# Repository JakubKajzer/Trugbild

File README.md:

# Trugbild
A FPGA working in serial with HDMI, for some real live video modifications. I'm making it to prove myself, that I can route highspeed PCB and to learn to code FPGA better.

## Features

- Xilinx Spartan 3 XC3S50A
- 2MB Flash memory
- 32MB DRAM memory
- Possibility to power device only from HDMI or from external input

## PCB screenshots
|||
|---|---|
## Why "Trugbild"
It is because Trugbild is a german word meaning _illusion_. So I think that is a good name for device which can modify what you see :)

## Develop steps
- [x] Make PCB

- [x] Order PCB fabrication
- [ ] Order elements
- [ ] Solder everything
- [ ] First run
- [ ] Try to run device only with power from HDMI (max. 50mA@5V)
- [ ] Make and test if device can transmit HDMI at Full HD
- [ ] Make some video modification while transmitting
- [ ] Try to add some kind of neuron network to face recognition
- [ ] Try to cover detected faces with some picture or someone face :)
## Comments
### Make PCB
This point took me many hours of designing because this is my first design with FPGA, so I had pretty much to learn. I'm still not sure if everything was routed least good, but I will find it out soon.
### Order PCB fabrication
For this, I used JLCPCB. They have 3.5mils clearance and track width, 0.2mm holes minimum, and four layers just for 8$. That's incredible!
But after uploading gerber files, it comes that they don't have 3.5mils clearance, but 0.09mm (3.543mils), so I must re-route some nets on PCB :( The 5 PCBs cost me total of $15.89 with delivery included.

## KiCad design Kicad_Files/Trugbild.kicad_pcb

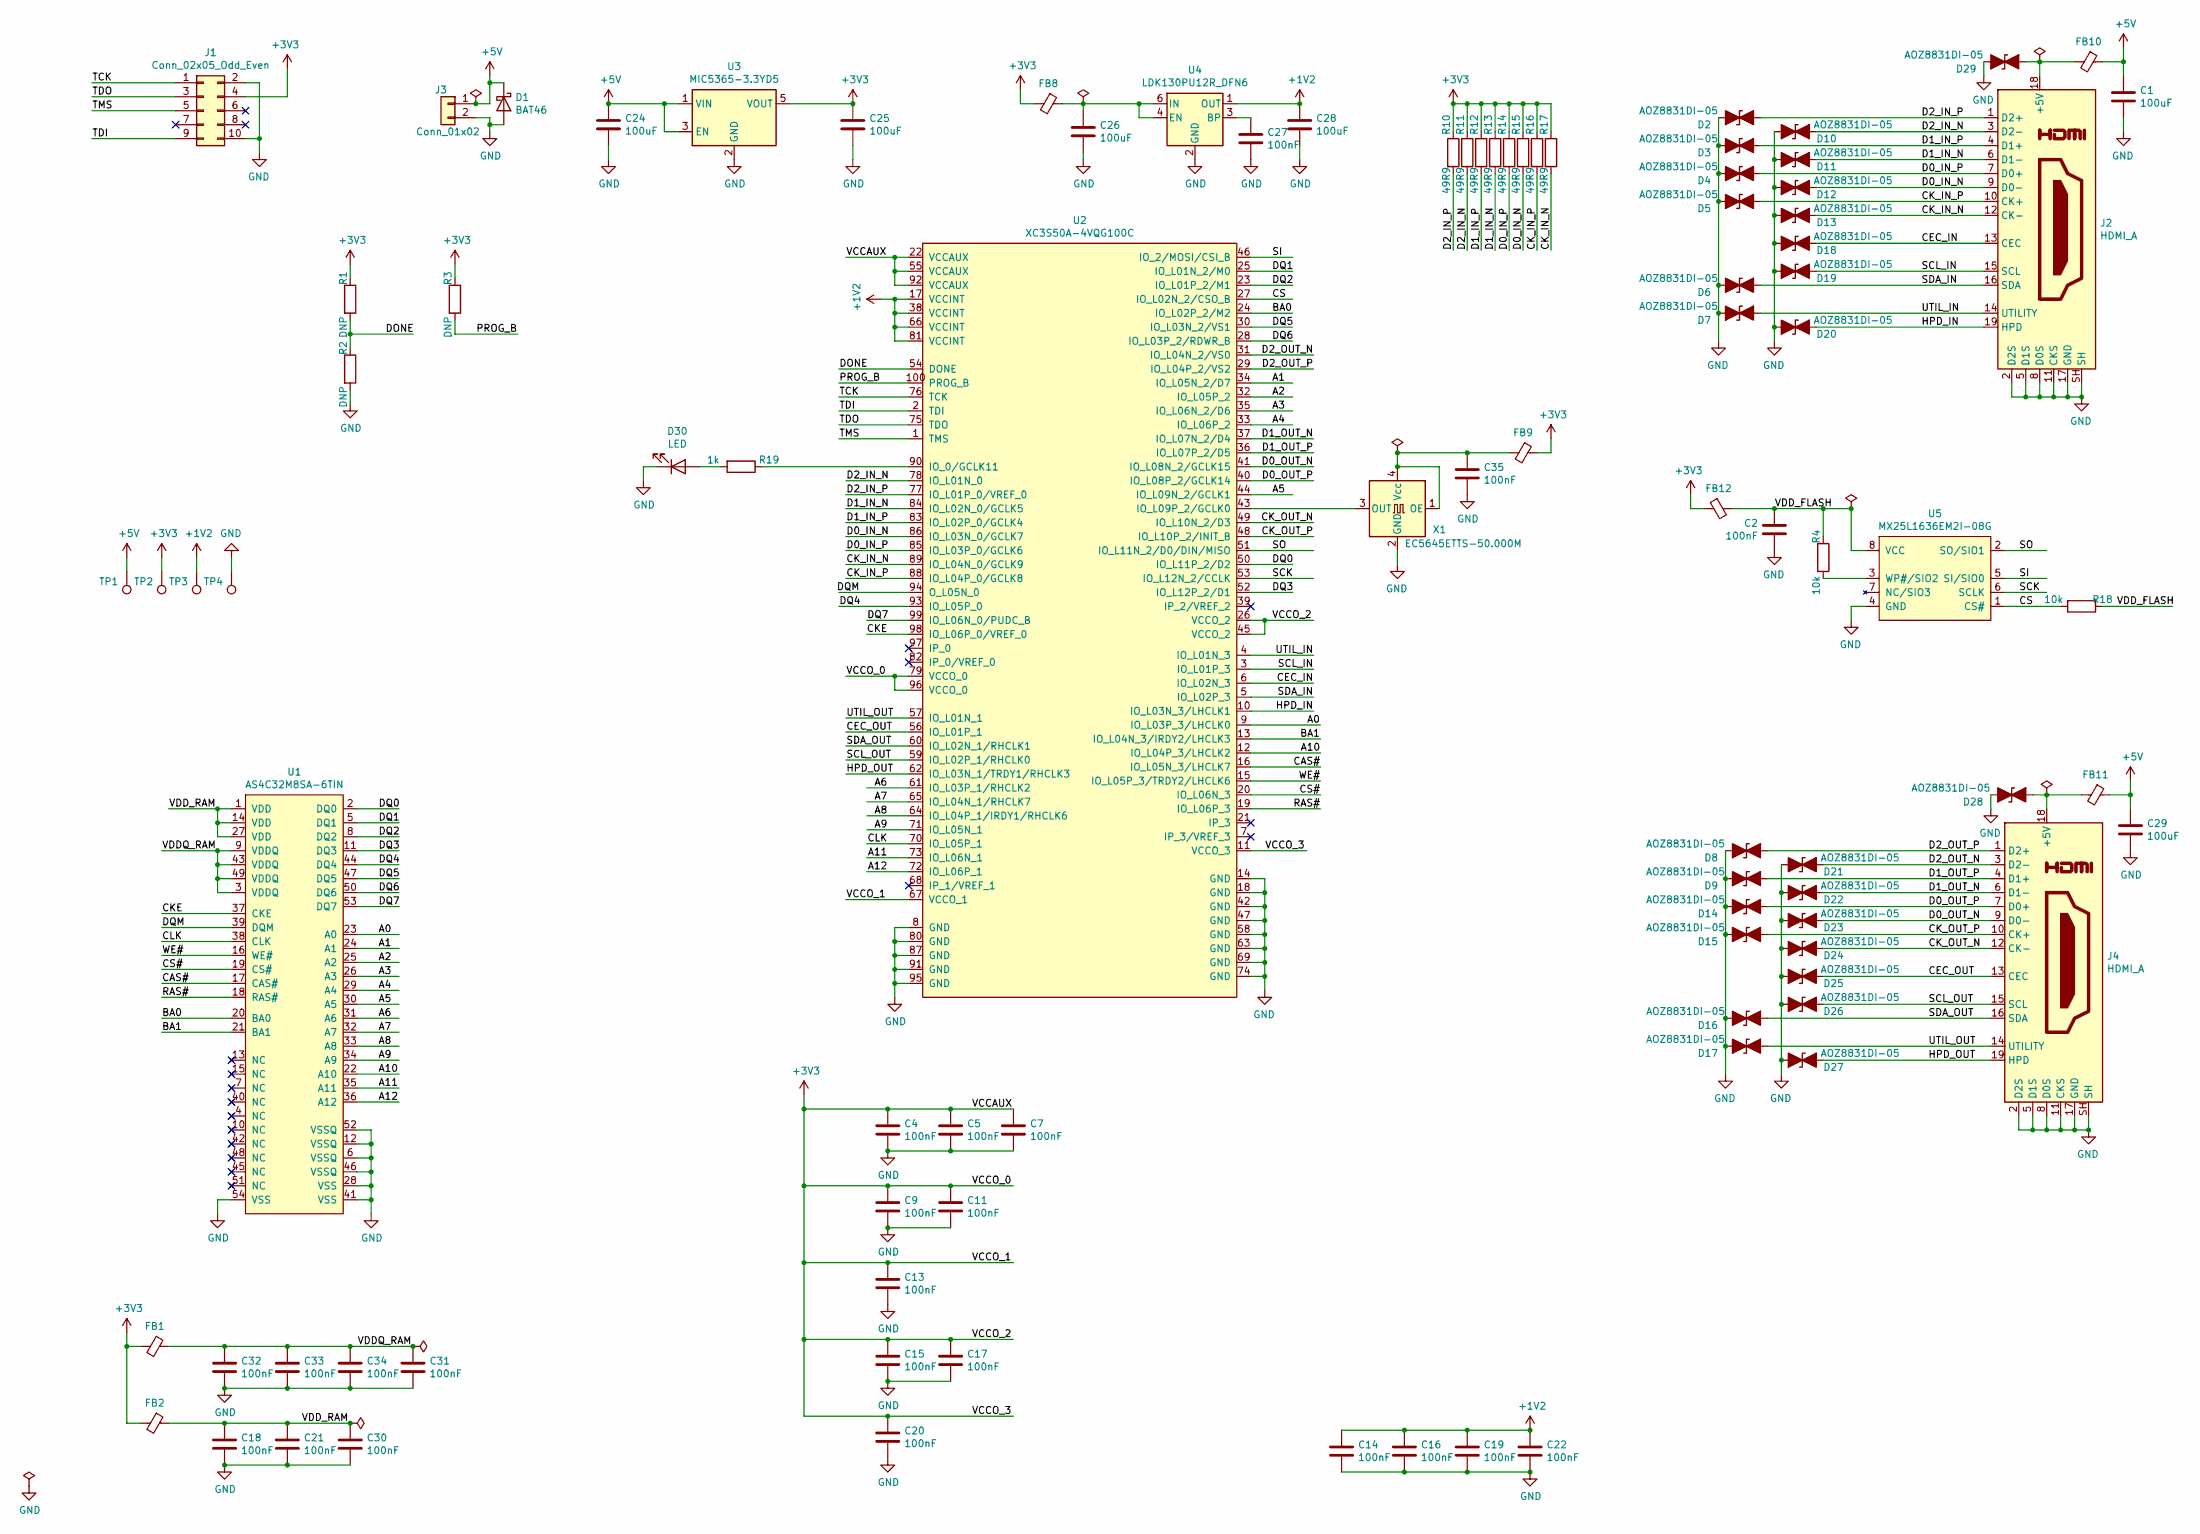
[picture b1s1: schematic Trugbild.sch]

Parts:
C1, C24, C25, C26, C28, C29: 100uF; C_0603_1608Metric
C2, C4, C5, C7, C9, C11, C13, C14, C15, C16, C17, C18, C19, C20, C21, C22, C27, C30, C31, C32, C33, C34, C35: 100nF; C_0402_1005Metric
D1: BAT46; D_SOD-123
D2, D3, D4, D5, D6, D7, D8, D9, D10, D11, D12, D13, D14, D15, D16, D17, D18, D19, D20, D21, D22, D23, D24, D25, D26, D27, D28, D29: AOZ8831DI-05; DFN-2
D30: LED; LED_0603_1608Metric
FB1, FB2, FB8, FB9, FB10, FB11, FB12: Ferrite_Bead_Small; L_0603_1608Metric
J1: Conn_02x05_Odd_Even; PinHeader_2x05_P2.54mm_Vertical
J2, J4: HDMI_A; AMPHENOL_10029449-001RLF
J3: Conn_01x02; PinHeader_1x02_P2.54mm_Vertical
R1, R2, R3: DNP; R_0402_1005Metric
R4, R18: 10k; R_0402_1005Metric
R10, R11, R12, R13, R14, R15, R16, R17: 49R9; R_0201_0603Metric
R19: 1k; R_0402_1005Metric
TP1, TP2, TP3, TP4: TestPoint; TestPoint_Pad_D1.0mm
U1: AS4C32M8SA-6TIN; TSOP-II-54_22.2x10.16mm_P0.8mm
U2: XC3S50A-4VQG100C; VQFP-100_14x14mm_P0.5mm
U3: MIC5365-3.3YD5; SOT-23-5
U4: LDK130PU12R_DFN6; DFN-6_1.3x1.2mm_P0.4mm
U5: MX25L1636EM2I-08G; SOP-8_5.28x5.23mm_P1.27mm
X1: EC5645ETTS-50.000M; Oscillator_SMD_SeikoEpson_SG8002CE-4Pin_3.2x2.5mm

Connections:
+1V2: C14.1, C16.1, C19.1, C22.1, C28.1, TP3.1, U2.17 (VCCINT), U2.38 (VCCINT), U2.66 (VCCINT), U2.81 (VCCINT), U4.1 (OUT); also elsewhere on the board
+3V3: C4.1, C5.1, C7.1, C9.1, C11.1, C13.1, C15.1, C17.1, C20.1, C25.1, FB1.2, FB2.2, FB8.2, FB9.1, FB12.1, J1.4, R1.1, R3.1, R10.1, R11.1, R12.1, R13.1, R14.1, R15.1, R16.1, R17.1, TP2.1, U2.11 (VCCO_3), U2.22 (VCCAUX), U2.26 (VCCO_2), U2.45 (VCCO_2), U2.55 (VCCAUX), U2.67 (VCCO_1), U2.79 (VCCO_0), U2.92 (VCCAUX), U2.96 (VCCO_0), U3.5 (VOUT); also elsewhere on the board
+5V: C1.1, C24.1, C29.1, D1.1 (K), FB10.1, FB11.1, J3.1, TP1.1, U3.1 (VIN), U3.3 (EN); also elsewhere on the board
/A0: U1.23 (A0), U2.9 (IO_L03P_3/LHCLK0)
/A1: U1.24 (A1), U2.34 (IO_L05N_2/D7)
/A2: U1.25 (A2), U2.32 (IO_L05P_2)
/A3: U1.26 (A3), U2.35 (IO_L06N_2/D6)
/A4: U1.29 (A4), U2.33 (IO_L06P_2)
/A5: U1.30 (A5), U2.44 (IO_L09N_2/GCLK1)
/A6: U1.31 (A6), U2.61 (IO_L03P_1/RHCLK2)
/A7: U1.32 (A7), U2.65 (IO_L04N_1/RHCLK7)
/A8: U1.33 (A8), U2.64 (IO_L04P_1/IRDY1/RHCLK6)
/A9: U1.34 (A9), U2.71 (IO_L05N_1)
/A10: U1.22 (A10), U2.12 (IO_L04P_3/LHCLK2)
/A11: U1.35 (A11), U2.73 (IO_L06N_1)
/A12: U1.36 (A12), U2.72 (IO_L06P_1)
/BA0: U1.20 (BA0), U2.24 (IO_L02P_2/M2)
/BA1: U1.21 (BA1), U2.13 (IO_L04N_3/IRDY2/LHCLK3)
/CAS#: U1.17 (CAS#), U2.16 (IO_L05N_3/LHCLK7)
/CEC_IN: D18.1 (A1), J2.13 (CEC), U2.6 (IO_L02N_3)
/CEC_OUT: D25.1 (A1), J4.13 (CEC), U2.56 (IO_L01P_1)
/CKE: U1.37 (CKE), U2.98 (IO_L06P_0/VREF_0)
/CK_IN_N: D13.1 (A1), J2.12 (CK-), R17.2, U2.89 (IO_L04N_0/GCLK9)
/CK_IN_P: D5.1 (A1), J2.10 (CK+), R16.2, U2.88 (IO_L04P_0/GCLK8)
/CK_OUT_N: D24.1 (A1), J4.12 (CK-), U2.49 (IO_L10N_2/D3)
/CK_OUT_P: D15.1 (A1), J4.10 (CK+), U2.48 (IO_L10P_2/INIT_B)
/CLK: U1.38 (CLK), U2.70 (IO_L05P_1)
/CS: R18.2, U2.27 (IO_L02N_2/CSO_B), U5.1 (CS#)
/CS#: U1.19 (CS#), U2.20 (IO_L06N_3)
/D0_IN_N: D12.1 (A1), J2.9 (D0-), R15.2, U2.86 (IO_L03N_0/GCLK7)
/D0_IN_P: D4.1 (A1), J2.7 (D0+), R14.2, U2.85 (IO_L03P_0/GCLK6)
/D0_OUT_N: D23.1 (A1), J4.9 (D0-), U2.41 (IO_L08N_2/GCLK15)
/D0_OUT_P: D14.1 (A1), J4.7 (D0+), U2.40 (IO_L08P_2/GCLK14)
/D1_IN_N: D11.1 (A1), J2.6 (D1-), R13.2, U2.84 (IO_L02N_0/GCLK5)
/D1_IN_P: D3.1 (A1), J2.4 (D1+), R12.2, U2.83 (IO_L02P_0/GCLK4)
/D1_OUT_N: D22.1 (A1), J4.6 (D1-), U2.37 (IO_L07N_2/D4)
/D1_OUT_P: D9.1 (A1), J4.4 (D1+), U2.36 (IO_L07P_2/D5)
/D2_IN_N: D10.1 (A1), J2.3 (D2-), R11.2, U2.78 (IO_L01N_0)
/D2_IN_P: D2.1 (A1), J2.1 (D2+), R10.2, U2.77 (IO_L01P_0/VREF_0)
/D2_OUT_N: D21.1 (A1), J4.3 (D2-), U2.31 (IO_L04N_2/VS0)
/D2_OUT_P: D8.1 (A1), J4.1 (D2+), U2.29 (IO_L04P_2/VS2)
/DONE: R1.2, R2.1, U2.54 (DONE)
/DQ0: U1.2 (DQ0), U2.50 (IO_L11P_2/D2)
/DQ1: U1.5 (DQ1), U2.25 (IO_L01N_2/M0)
/DQ2: U1.8 (DQ2), U2.23 (IO_L01P_2/M1)
/DQ3: U1.11 (DQ3), U2.52 (IO_L12P_2/D1)
/DQ4: U1.44 (DQ4), U2.93 (IO_L05P_0)
/DQ5: U1.47 (DQ5), U2.30 (IO_L03N_2/VS1)
/DQ6: U1.50 (DQ6), U2.28 (IO_L03P_2/RDWR_B)
/DQ7: U1.53 (DQ7), U2.99 (IO_L06N_0/PUDC_B)
/DQM: U1.39 (DQM), U2.94 (O_L05N_0)
/HPD_IN: D20.1 (A1), J2.19 (HPD), U2.10 (IO_L03N_3/LHCLK1)
/HPD_OUT: D27.1 (A1), J4.19 (HPD), U2.62 (IO_L03N_1/TRDY1/RHCLK3)
/PROG_B: R3.2, U2.100 (PROG_B)
/RAS#: U1.18 (RAS#), U2.19 (IO_L06P_3)
/SCK: U2.53 (IO_L12N_2/CCLK), U5.6 (SCLK)
/SCL_IN: D19.1 (A1), J2.15 (SCL), U2.3 (IO_L01P_3)
/SCL_OUT: D26.1 (A1), J4.15 (SCL), U2.59 (IO_L02P_1/RHCLK0)
/SDA_IN: D6.1 (A1), J2.16 (SDA), U2.5 (IO_L02P_3)
/SDA_OUT: D16.1 (A1), J4.16 (SDA), U2.60 (IO_L02N_1/RHCLK1)
/SI: U2.46 (IO_2/MOSI/CSI_B), U5.5 (SI/SIO0)
/SO: U2.51 (IO_L11N_2/D0/DIN/MISO), U5.2 (SO/SIO1)
/TCK: J1.1, U2.76 (TCK)
/TDI: J1.9, U2.2 (TDI)
/TDO: J1.3, U2.75 (TDO)
/TMS: J1.5, U2.1 (TMS)
/UTIL_IN: D7.1 (A1), J2.14 (UTILITY), U2.4 (IO_L01N_3)
/UTIL_OUT: D17.1 (A1), J4.14 (UTILITY), U2.57 (IO_L01N_1)
/VDDQ_RAM: C31.1, C32.1, C33.1, C34.1, FB1.1, U1.3 (VDDQ), U1.9 (VDDQ), U1.43 (VDDQ), U1.49 (VDDQ)
/VDD_FLASH: C2.1, FB12.2, R4.1, R18.1, U5.8 (VCC)
/VDD_RAM: C18.1, C21.1, C30.1, FB2.1, U1.1 (VDD), U1.14 (VDD), U1.27 (VDD)
/WE#: U1.16 (WE#), U2.15 (IO_L05P_3/TRDY2/LHCLK6)
GND: C1.2, C2.2, C4.2, C5.2, C7.2, C9.2, C11.2, C13.2, C14.2, C15.2, C16.2, C17.2, C18.2, C19.2, C20.2, C21.2, C22.2, C24.2, C25.2, C26.2, C27.2, C28.2, C29.2, C30.2, C31.2, C32.2, C33.2, C34.2, C35.2, D1.2 (A), D2.2 (A2), D3.2 (A2), D4.2 (A2), D5.2 (A2), D6.2 (A2), D7.2 (A2), D8.2 (A2), D9.2 (A2), D10.2 (A2), D11.2 (A2), D12.2 (A2), D13.2 (A2), D14.2 (A2), D15.2 (A2), D16.2 (A2), D17.2 (A2), D18.2 (A2), D19.2 (A2), D20.2 (A2), D21.2 (A2), D22.2 (A2), D23.2 (A2), D24.2 (A2), D25.2 (A2), D26.2 (A2), D27.2 (A2), D28.2 (A2), D29.2 (A2), D30.1 (K), J1.2, J1.10, J2.2 (D2S), J2.5 (D1S), J2.8 (D0S), J2.11 (CKS), J2.17 (GND), J2.SH, J3.2, J4.2 (D2S), J4.5 (D1S), J4.8 (D0S), J4.11 (CKS), J4.17 (GND), J4.SH, R2.2, TP4.1, U1.6 (VSSQ), U1.12 (VSSQ), U1.28 (VSS), U1.41 (VSS), U1.46 (VSSQ), U1.52 (VSSQ), U1.54 (VSS), U2.8 (GND), U2.14 (GND), U2.18 (GND), U2.42 (GND), U2.47 (GND), U2.58 (GND), U2.63 (GND), U2.69 (GND), U2.74 (GND), U2.80 (GND), U2.87 (GND), U2.91 (GND), U2.95 (GND), U3.2 (GND), U4.2 (GND), U5.4 (GND), X1.2 (GND); also elsewhere on the board
unnamed: C26.1, FB8.1, U4.4 (EN), U4.6 (IN)
unnamed: C27.1, U4.3 (BP)
unnamed: C35.1, FB9.2, X1.1 (OE), X1.4 (Vcc)
unnamed: D28.1 (A1), FB11.2, J4.18 (+5V)
unnamed: D29.1 (A1), FB10.2, J2.18 (+5V)
unnamed: D30.2 (A), R19.2
unnamed: R4.2, U5.3 (WP#/SIO2)
unnamed: R19.1, U2.90 (IO_0/GCLK11)
unnamed: U2.43 (IO_L09P_2/GCLK0), X1.3 (OUT)

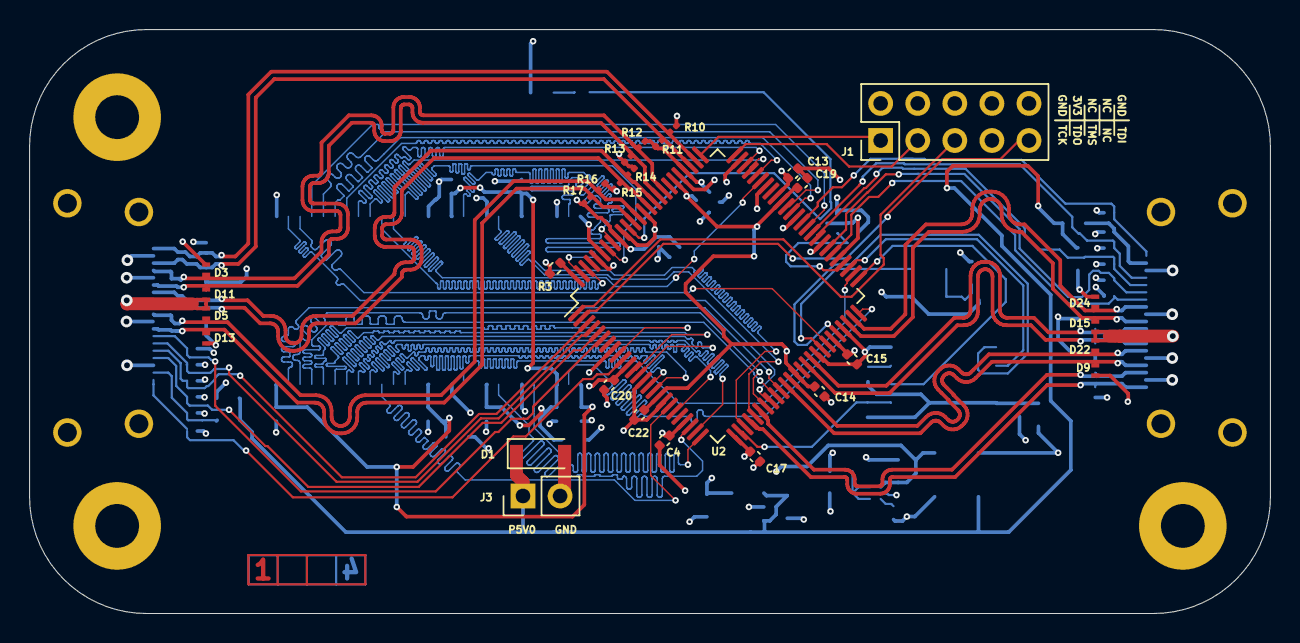
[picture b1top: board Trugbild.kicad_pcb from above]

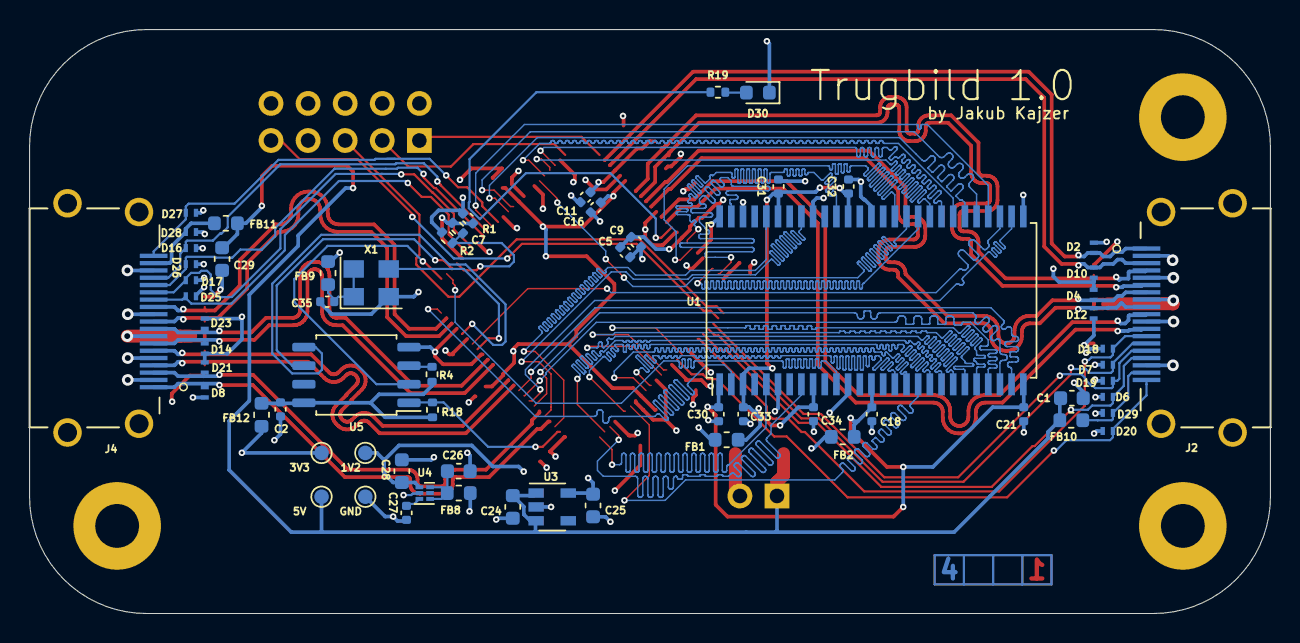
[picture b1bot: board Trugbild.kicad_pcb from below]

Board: 4 copper layers, 85.0 x 40.0 mm, 94 parts (65 on the bottom side), 82 nets.

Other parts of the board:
1V2, 3V3, 5V: TestPoint; TestPoint_Pad_D1.0mm
GND: TestPoint; TestPoint_Pad_D1.0mm

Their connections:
+1V2: 1V2.1; also elsewhere on the board
+3V3: 3V3.1; also elsewhere on the board
+5V: 5V.1; also elsewhere on the board
GND: GND.1; also elsewhere on the board

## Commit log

2021-07-15 Init
2021-07-15 Fabrication update and images
2021-07-15 repaired readme
2021-07-15 fix images
2021-07-24 fix for JLCPCB clearance
2021-07-24 fix for clearance v2
